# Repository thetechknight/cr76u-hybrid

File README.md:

# cr76u-hybrid
CR-76D Shin EI IC Recreation for the Sony CR-76U Power Supply used in the Macintosh Portable

BOM Link to Mouser is here: 
https://www.mouser.com/ProjectManager/ProjectDetail.aspx?AccessID=344d339bbd

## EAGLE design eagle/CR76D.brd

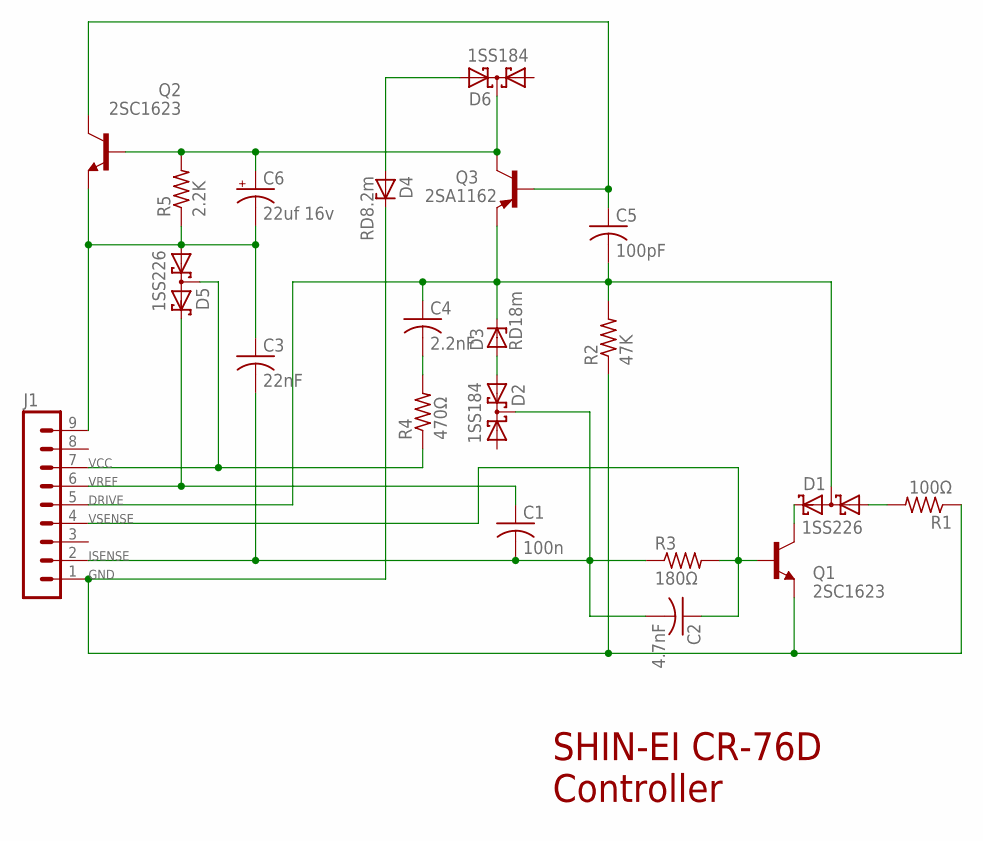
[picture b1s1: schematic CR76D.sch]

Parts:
C1: 100n; C1206
C2: 4.7nF; C0805
C3: 22nF; C0805
C4: 2.2nF; C0805
C5: 100pF; C0805
C6: 22uf 16v; B/3528-21W
D1, D5: 1SS226; SOT23
D2, D6: 1SS184; SOT23
D3: RD18m; SOT23
D4: RD8.2m; SOT23
J1: MA09-1
Q1, Q2: 2SC1623; SOT23-BEC
Q3: 2SA1162; SOT23
R1: 100Ω; R0805W
R2: 47K; R0805W
R3: 180Ω; R0805W
R4: 470Ω; R0805W
R5: 2.2K; R0805W

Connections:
DRIVE: C4.1, C5.2, D1.3 (C1A2), D3.3 (C), J1.5, Q3.2 (E), R2.2
GND: D4.3 (C), J1.1, Q1.E, R1.1, R2.1
ISENSE: C1.2, C2.2, C3.2, D2.3 (C), J1.2, R3.1
unnamed: D2.2 (A2), D3.1 (A)
unnamed: C4.2, R4.2
unnamed: D1.2 (C2), Q1.C
unnamed: D1.1 (A1), R1.2
unnamed: C3.1, C6.-, D5.1 (A1), J1.9, Q2.E, R5.1
unnamed: C6.+, D6.3 (C), Q2.B, Q3.3 (C), R5.2
unnamed: D4.1 (A), D6.2 (A2)
unnamed: C5.1, Q2.C, Q3.1 (B)
VCC: D5.3 (C1A2), J1.7, R4.1
VREF: C1.1, D5.2 (C2), J1.6
VSENSE: C2.1, J1.4, Q1.B, R3.2

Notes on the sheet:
SHIN-EI CR-76D Controller

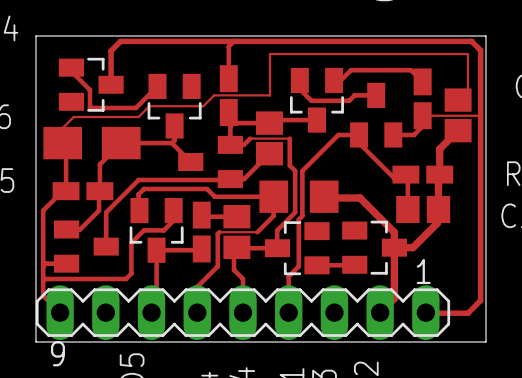
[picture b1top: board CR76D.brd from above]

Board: 2 copper layers, 25.0 x 17.0 mm, 22 parts (1 on the bottom side), 14 nets.

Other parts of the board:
U$1: LOGO

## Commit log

2024-12-13 Create file
2024-12-13 Added Gerbers
2024-12-13 Added schematics
2024-12-13 Update LICENSE
